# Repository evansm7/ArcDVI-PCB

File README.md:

# ArcDVI VIDC adapter PCBs
30 November 2021

Two PCBs used in the [ArcDVI](https://github.com/evansm7/ArcDVI) project.

These PCBs (#1 and #2) both perform the task of physical interfacing to an Acorn Archimedes VIDC chip, but for different machines.  PCB #1 is an interposer for VIDC-socketed machines (such as A440), which plugs into the VIDC socket and carries a socket for the VIDC.  PCB #2 uses an upturned through-hole PLCC socket to clip around a soldered VIDC (in machines such as A3000).

[vidc_interposer1 schematic](doc/vidc_interposer1.pdf), [vidc_interposer1 board](doc/vidc_interposer1_brd.pdf), [vidc_interposer2 schematic](doc/vidc_interposer2-PTH.pdf),
[vidc_interposer2 board](doc/vidc_interposer2-PTH_brd.pdf)

It was originally hoped that PCB #1 could be used on an A3000 too, with an SMT PLCC socket on the bottom (and nothing mounted on the top).  Those sockets are shallow, and the board level is then too low to clear surrounding components.  (Note there are two odd holes in the board; this was to clear some jumper headers.  These were unnecessarily carried into PCB #2's layout too.  In short, neither board needs these holes anymore.)

A separate project (TBD) is recreating PLCC socket-to-socket interface "blocks", enabling a PLCC socket (rather than plug) to be used on the underside of board #1.

The PCBs are designed in Eagle.

Copyright 2021 Matt Evans

CC BY-SA 3.0

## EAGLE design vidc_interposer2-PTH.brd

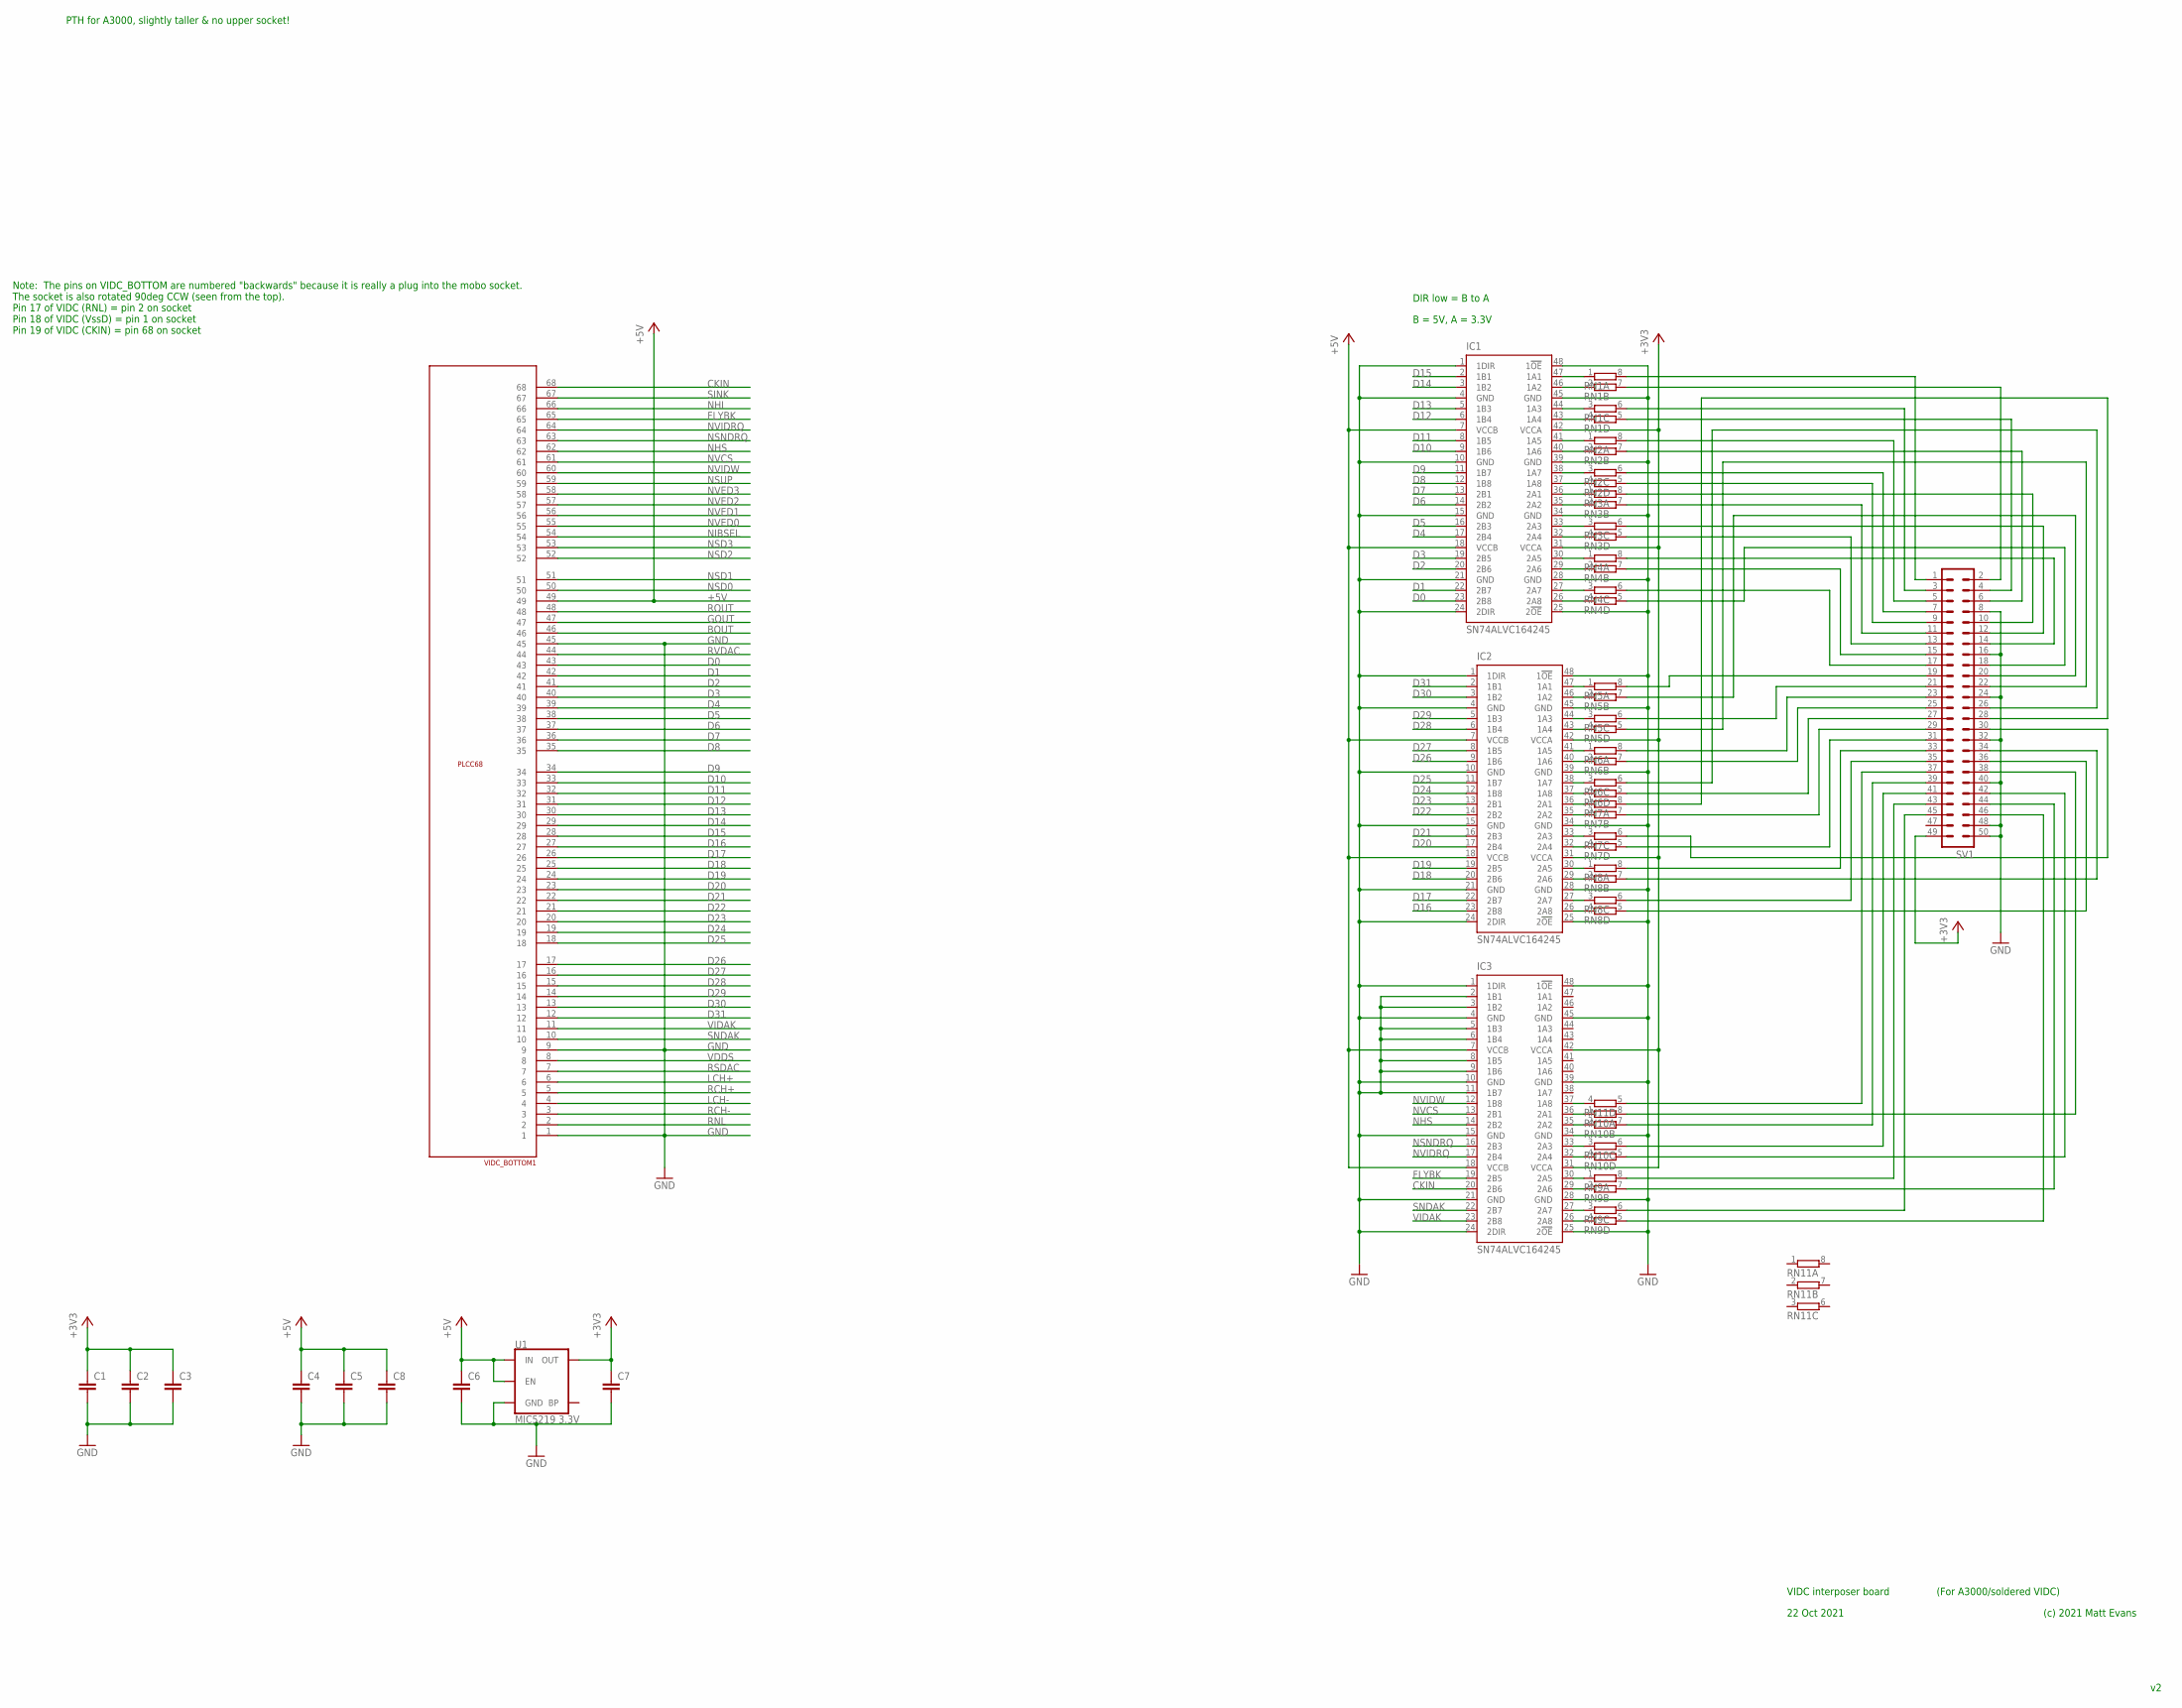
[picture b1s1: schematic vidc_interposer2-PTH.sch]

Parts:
C1, C2, C3, C4, C5, C6, C7, C8: C-EUC0805; C0805
IC1, IC2, IC3: SN74ALVC164245; DL_R-PDSO-G48
RN1, RN2, RN3, RN4, RN5, RN6, RN7, RN8, RN9, RN10, RN11: 4R-NCAY16; CAY16
SV1: ML50
U1: MIC5219 3.3V; SOT23-5
VIDC_BOTTOM1: RAW_PLCC68PTH; S68

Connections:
+3V3: C1.1, C2.1, C3.1, C7.1, IC1.31 (VCCA), IC1.42 (VCCA), IC2.31 (VCCA), IC2.42 (VCCA), IC3.31 (VCCA), IC3.42 (VCCA), SV1.49, U1.5 (OUT)
+5V: C4.1, C5.1, C6.1, C8.1, IC1.7 (VCCB), IC1.18 (VCCB), IC2.7 (VCCB), IC2.18 (VCCB), IC3.7 (VCCB), IC3.18 (VCCB), U1.1 (IN), U1.3 (EN), VIDC_BOTTOM1.49
BOUT: VIDC_BOTTOM1.46
CKIN: IC3.20 (2B6), VIDC_BOTTOM1.68
D0: IC1.23 (2B8), VIDC_BOTTOM1.43
D1: IC1.22 (2B7), VIDC_BOTTOM1.42
D2: IC1.20 (2B6), VIDC_BOTTOM1.41
D3: IC1.19 (2B5), VIDC_BOTTOM1.40
D4: IC1.17 (2B4), VIDC_BOTTOM1.39
D5: IC1.16 (2B3), VIDC_BOTTOM1.38
D6: IC1.14 (2B2), VIDC_BOTTOM1.37
D7: IC1.13 (2B1), VIDC_BOTTOM1.36
D8: IC1.12 (1B8), VIDC_BOTTOM1.35
D9: IC1.11 (1B7), VIDC_BOTTOM1.34
D10: IC1.9 (1B6), VIDC_BOTTOM1.33
D11: IC1.8 (1B5), VIDC_BOTTOM1.32
D12: IC1.6 (1B4), VIDC_BOTTOM1.31
D13: IC1.5 (1B3), VIDC_BOTTOM1.30
D14: IC1.3 (1B2), VIDC_BOTTOM1.29
D15: IC1.2 (1B1), VIDC_BOTTOM1.28
D16: IC2.23 (2B8), VIDC_BOTTOM1.27
D17: IC2.22 (2B7), VIDC_BOTTOM1.26
D18: IC2.20 (2B6), VIDC_BOTTOM1.25
D19: IC2.19 (2B5), VIDC_BOTTOM1.24
D20: IC2.17 (2B4), VIDC_BOTTOM1.23
D21: IC2.16 (2B3), VIDC_BOTTOM1.22
D22: IC2.14 (2B2), VIDC_BOTTOM1.21
D23: IC2.13 (2B1), VIDC_BOTTOM1.20
D24: IC2.12 (1B8), VIDC_BOTTOM1.19
D25: IC2.11 (1B7), VIDC_BOTTOM1.18
D26: IC2.9 (1B6), VIDC_BOTTOM1.17
D27: IC2.8 (1B5), VIDC_BOTTOM1.16
D28: IC2.6 (1B4), VIDC_BOTTOM1.15
D29: IC2.5 (1B3), VIDC_BOTTOM1.14
D30: IC2.3 (1B2), VIDC_BOTTOM1.13
D31: IC2.2 (1B1), VIDC_BOTTOM1.12
FLYBK: IC3.19 (2B5), VIDC_BOTTOM1.65
GND: C1.2, C2.2, C3.2, C4.2, C5.2, C6.2, C7.2, C8.2, IC1.1 (1DIR), IC1.4 (GND), IC1.10 (GND), IC1.15 (GND), IC1.21 (GND), IC1.24 (2DIR), IC1.25 (2!OE), IC1.28 (GND), IC1.34 (GND), IC1.39 (GND), IC1.45 (GND), IC1.48 (1!OE), IC2.1 (1DIR), IC2.4 (GND), IC2.10 (GND), IC2.15 (GND), IC2.21 (GND), IC2.24 (2DIR), IC2.25 (2!OE), IC2.28 (GND), IC2.34 (GND), IC2.39 (GND), IC2.45 (GND), IC2.48 (1!OE), IC3.1 (1DIR), IC3.2 (1B1), IC3.3 (1B2), IC3.4 (GND), IC3.5 (1B3), IC3.6 (1B4), IC3.8 (1B5), IC3.9 (1B6), IC3.10 (GND), IC3.11 (1B7), IC3.15 (GND), IC3.21 (GND), IC3.24 (2DIR), IC3.25 (2!OE), IC3.28 (GND), IC3.34 (GND), IC3.39 (GND), IC3.45 (GND), IC3.48 (1!OE), SV1.8, SV1.16, SV1.24, SV1.32, SV1.40, SV1.48, SV1.50, U1.2 (GND), VIDC_BOTTOM1.1, VIDC_BOTTOM1.9, VIDC_BOTTOM1.45
GOUT: VIDC_BOTTOM1.47
LCH+: VIDC_BOTTOM1.6
LCH-: VIDC_BOTTOM1.4
unnamed: IC3.26 (2A8), RN9.4 (1)
unnamed: IC3.27 (2A7), RN9.3 (1)
unnamed: IC3.29 (2A6), RN9.2 (1)
unnamed: IC3.30 (2A5), RN9.1
unnamed: IC3.32 (2A4), RN10.4 (1)
unnamed: IC3.33 (2A3), RN10.3 (1)
unnamed: IC3.35 (2A2), RN10.2 (1)
unnamed: IC3.36 (2A1), RN10.1
unnamed: IC1.47 (1A1), RN1.1
unnamed: IC1.46 (1A2), RN1.2 (1)
unnamed: IC1.44 (1A3), RN1.3 (1)
unnamed: IC1.43 (1A4), RN1.4 (1)
unnamed: IC1.41 (1A5), RN2.1
unnamed: IC1.40 (1A6), RN2.2 (1)
unnamed: IC1.38 (1A7), RN2.3 (1)
unnamed: IC1.37 (1A8), RN2.4 (1)
unnamed: IC1.36 (2A1), RN3.1
unnamed: IC1.35 (2A2), RN3.2 (1)
unnamed: IC1.33 (2A3), RN3.3 (1)
unnamed: IC1.32 (2A4), RN3.4 (1)
unnamed: IC1.30 (2A5), RN4.1
unnamed: IC1.29 (2A6), RN4.2 (1)
unnamed: IC3.37 (1A8), RN11.4 (1)
unnamed: IC1.27 (2A7), RN4.3 (1)
unnamed: IC1.26 (2A8), RN4.4 (1)
unnamed: IC2.47 (1A1), RN5.1
unnamed: IC2.46 (1A2), RN5.2 (1)
unnamed: IC2.44 (1A3), RN5.3 (1)
unnamed: IC2.43 (1A4), RN5.4 (1)
unnamed: IC2.41 (1A5), RN6.1
unnamed: IC2.40 (1A6), RN6.2 (1)
unnamed: IC2.38 (1A7), RN6.3 (1)
unnamed: IC2.37 (1A8), RN6.4 (1)
unnamed: IC2.36 (2A1), RN7.1
unnamed: IC2.35 (2A2), RN7.2 (1)
unnamed: IC2.33 (2A3), RN7.3 (1)
unnamed: IC2.32 (2A4), RN7.4 (1)
unnamed: IC2.30 (2A5), RN8.1
unnamed: IC2.29 (2A6), RN8.2 (1)
unnamed: IC2.27 (2A7), RN8.3 (1)
unnamed: IC2.26 (2A8), RN8.4 (1)
unnamed: RN1.8 (2), SV1.1
unnamed: RN1.7 (2), SV1.2
unnamed: RN1.6 (2), SV1.3
unnamed: RN1.5 (2), SV1.4
unnamed: RN5.8 (2), SV1.19
unnamed: RN2.8 (2), SV1.5
unnamed: RN2.7 (2), SV1.6
unnamed: RN2.6 (2), SV1.7
unnamed: RN2.5 (2), SV1.9
unnamed: RN3.7 (2), SV1.11
unnamed: RN5.7 (2), SV1.20
unnamed: RN3.8 (2), SV1.10
unnamed: RN3.5 (2), SV1.13
unnamed: RN3.6 (2), SV1.12
unnamed: RN4.7 (2), SV1.15
unnamed: RN4.8 (2), SV1.14
unnamed: RN4.6 (2), SV1.17
unnamed: RN5.5 (2), SV1.22
unnamed: RN5.6 (2), SV1.21
unnamed: RN4.5 (2), SV1.18
unnamed: RN8.5 (2), SV1.36
unnamed: RN10.8 (2), SV1.38
unnamed: RN6.6 (2), SV1.26
unnamed: RN6.8 (2), SV1.23
unnamed: RN7.8 (2), SV1.28
unnamed: RN6.7 (2), SV1.25
unnamed: RN11.5 (2), SV1.37
unnamed: RN10.5 (2), SV1.42
unnamed: RN6.5 (2), SV1.27
unnamed: RN10.7 (2), SV1.39
unnamed: RN9.7 (2), SV1.44
unnamed: RN9.8 (2), SV1.43
unnamed: RN7.7 (2), SV1.29
unnamed: RN9.6 (2), SV1.45
unnamed: RN7.6 (2), SV1.30
unnamed: RN8.7 (2), SV1.34
unnamed: RN10.6 (2), SV1.41
unnamed: RN7.5 (2), SV1.31
unnamed: RN8.8 (2), SV1.33
unnamed: RN8.6 (2), SV1.35
unnamed: RN9.5 (2), SV1.46
NHI: VIDC_BOTTOM1.66
NHS: IC3.14 (2B2), VIDC_BOTTOM1.62
NIBSEL: VIDC_BOTTOM1.54
NSD0: VIDC_BOTTOM1.50
NSD1: VIDC_BOTTOM1.51
NSD2: VIDC_BOTTOM1.52
NSD3: VIDC_BOTTOM1.53
NSNDRQ: IC3.16 (2B3), VIDC_BOTTOM1.63
NSUP: VIDC_BOTTOM1.59
NVCS: IC3.13 (2B1), VIDC_BOTTOM1.61
NVED0: VIDC_BOTTOM1.55
NVED1: VIDC_BOTTOM1.56
NVED2: VIDC_BOTTOM1.57
NVED3: VIDC_BOTTOM1.58
NVIDRQ: IC3.17 (2B4), VIDC_BOTTOM1.64
NVIDW: IC3.12 (1B8), VIDC_BOTTOM1.60
RCH+: VIDC_BOTTOM1.5
RCH-: VIDC_BOTTOM1.3
RNL: VIDC_BOTTOM1.2
ROUT: VIDC_BOTTOM1.48
RSDAC: VIDC_BOTTOM1.7
RVDAC: VIDC_BOTTOM1.44
SINK: VIDC_BOTTOM1.67
SNDAK: IC3.22 (2B7), VIDC_BOTTOM1.10
VDDS: VIDC_BOTTOM1.8
VIDAK: IC3.23 (2B8), VIDC_BOTTOM1.11

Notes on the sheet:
Note: The pins on VIDC_BOTTOM are numbered "backwards" because it is really a plug into the mobo socket. The socket is also rotated 90deg CCW (seen from the top). Pin 17 of VIDC (RNL) = pin 2 on socket Pin 18 of VIDC (VssD) = pin 1 on socket Pin 19 of VIDC (CKIN) = pin 68 on socket
DIR low = B to A
B = 5V, A = 3.3V
VIDC interposer board
22 Oct 2021
(c) 2021 Matt Evans
PTH for A3000, slightly taller & no upper socket!
(For A3000/soldered VIDC)

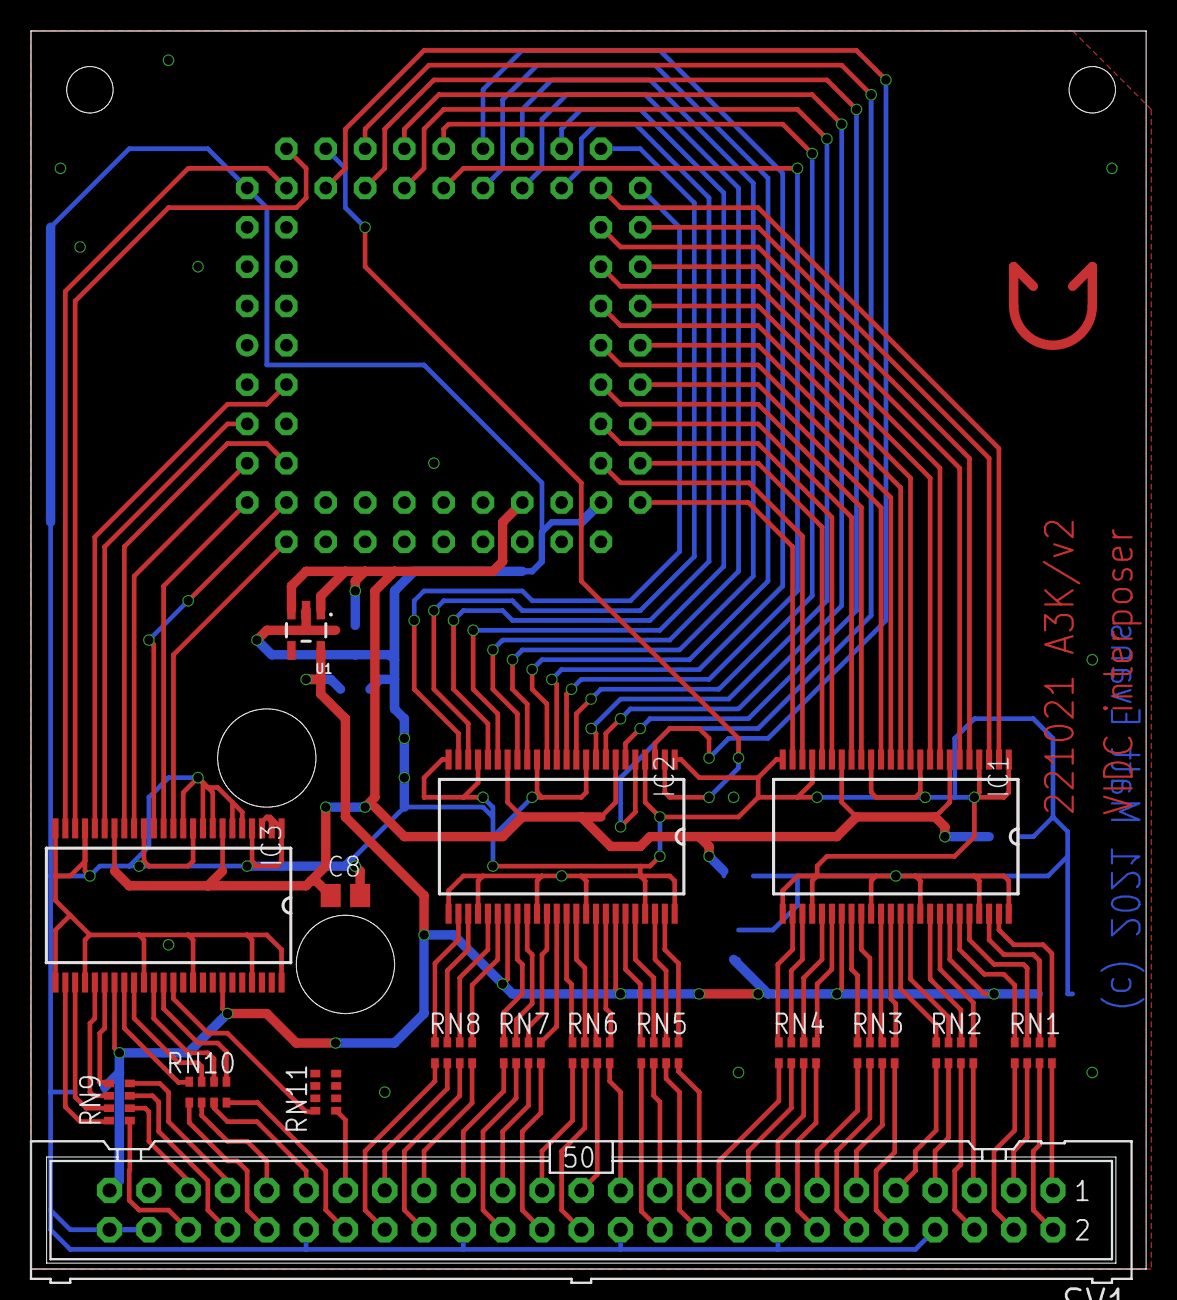
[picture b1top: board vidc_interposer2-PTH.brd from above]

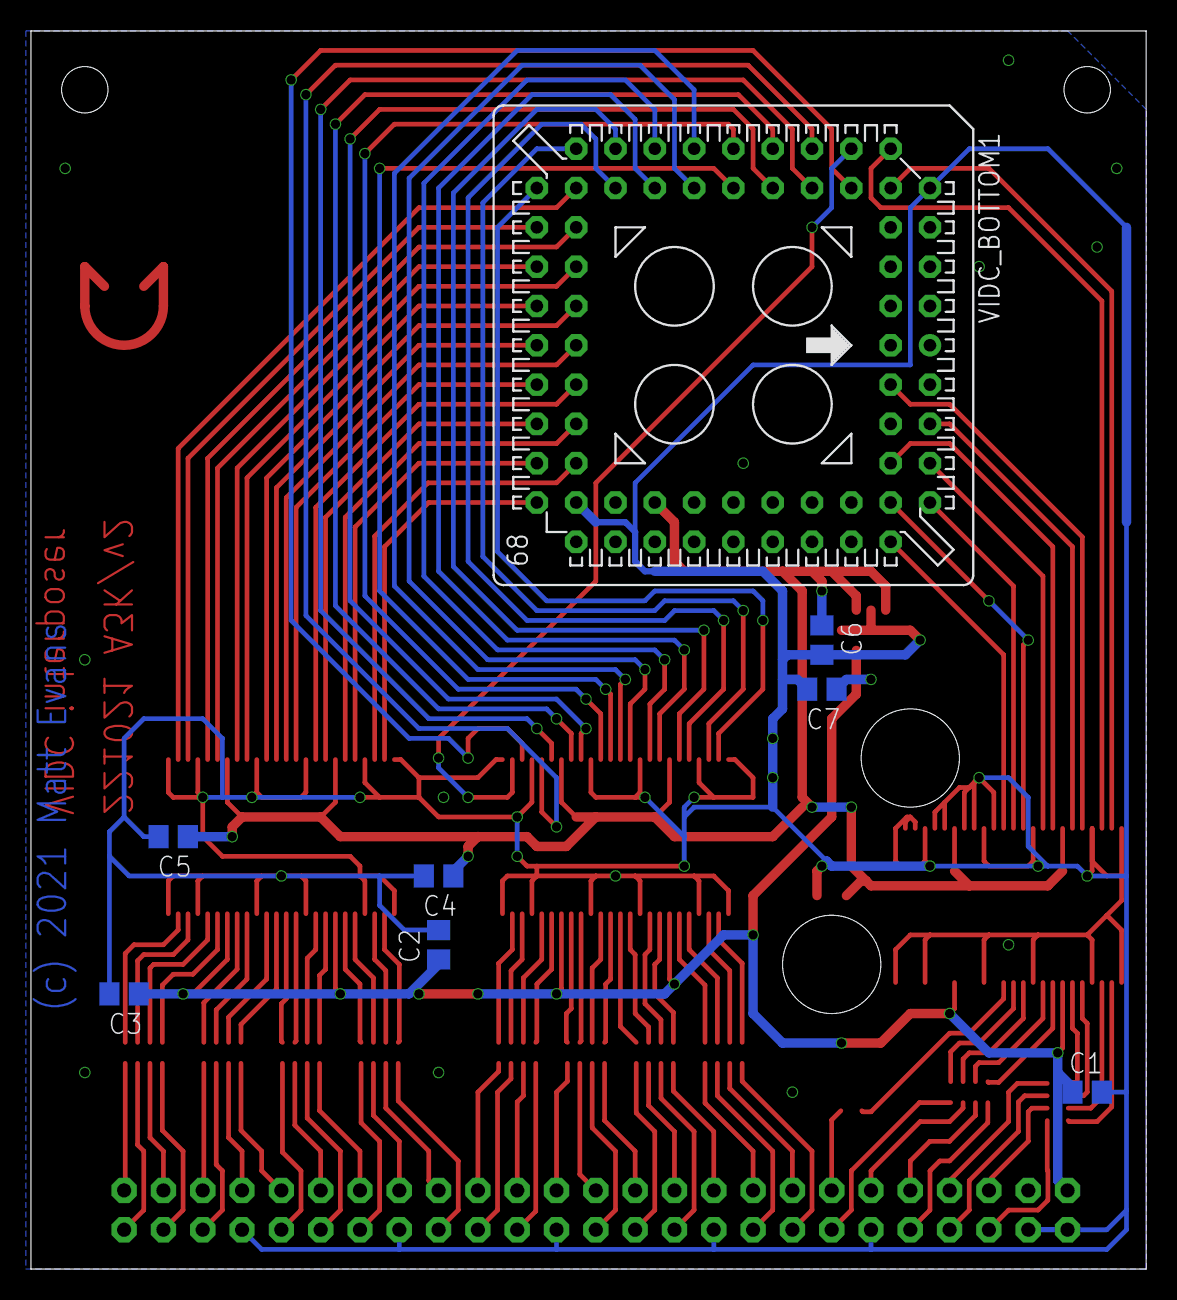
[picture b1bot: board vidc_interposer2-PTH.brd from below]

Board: 2 copper layers, 72.1 x 80.0 mm, 25 parts (8 on the bottom side), 126 nets.

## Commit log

2021-10-22 Original v1 interposer
2021-10-22 Add A3K/PTH 'v2' board
2021-11-30 Update schematics with licence
2021-11-30 Add schematic/board PDFs
2021-11-30 Add README
2021-12-04 README: Link to ArcDVI

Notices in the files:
parts and their libraries:
SparkFun-IC-Power: Licensing: Creative Commons ShareAlike 4.0 International - https://creativecommons.org/licenses/by-sa/4.0
